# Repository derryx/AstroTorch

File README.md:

# Astro-Torch

## Bestellnummern von Reichelt

* ATTINY 24A-SSU ( +2.7 ... +5.5 V, SOIC-14)
* LED 5-8000 RT (Kingbright L-7113SRC-J4, 2.5V, 20mA)
* LED EL 5-14250KW (Everlight 334-15/T2C3-2TVC/EU, 3.6V, 20mA)
* MCP 1703T-3302E (MCP1703T-3302E/CB, Low-Power Regulator 3.3V, SOT-23A)
* IRLML 2502 (IRLML2502TRPBF, N-Ch-Mosfet logic-level, SOT-23)
* Rotary Encoder STEC12E08 (402097) + Knopf KNOPF 13-164E (861036)
* Gehäuse SP 6090 SW 

Für den LDO Regulator 2X 1 uF Ceramic KEM 0805 1U (C0805C105K4RACAUTO, 0805 Bauform)

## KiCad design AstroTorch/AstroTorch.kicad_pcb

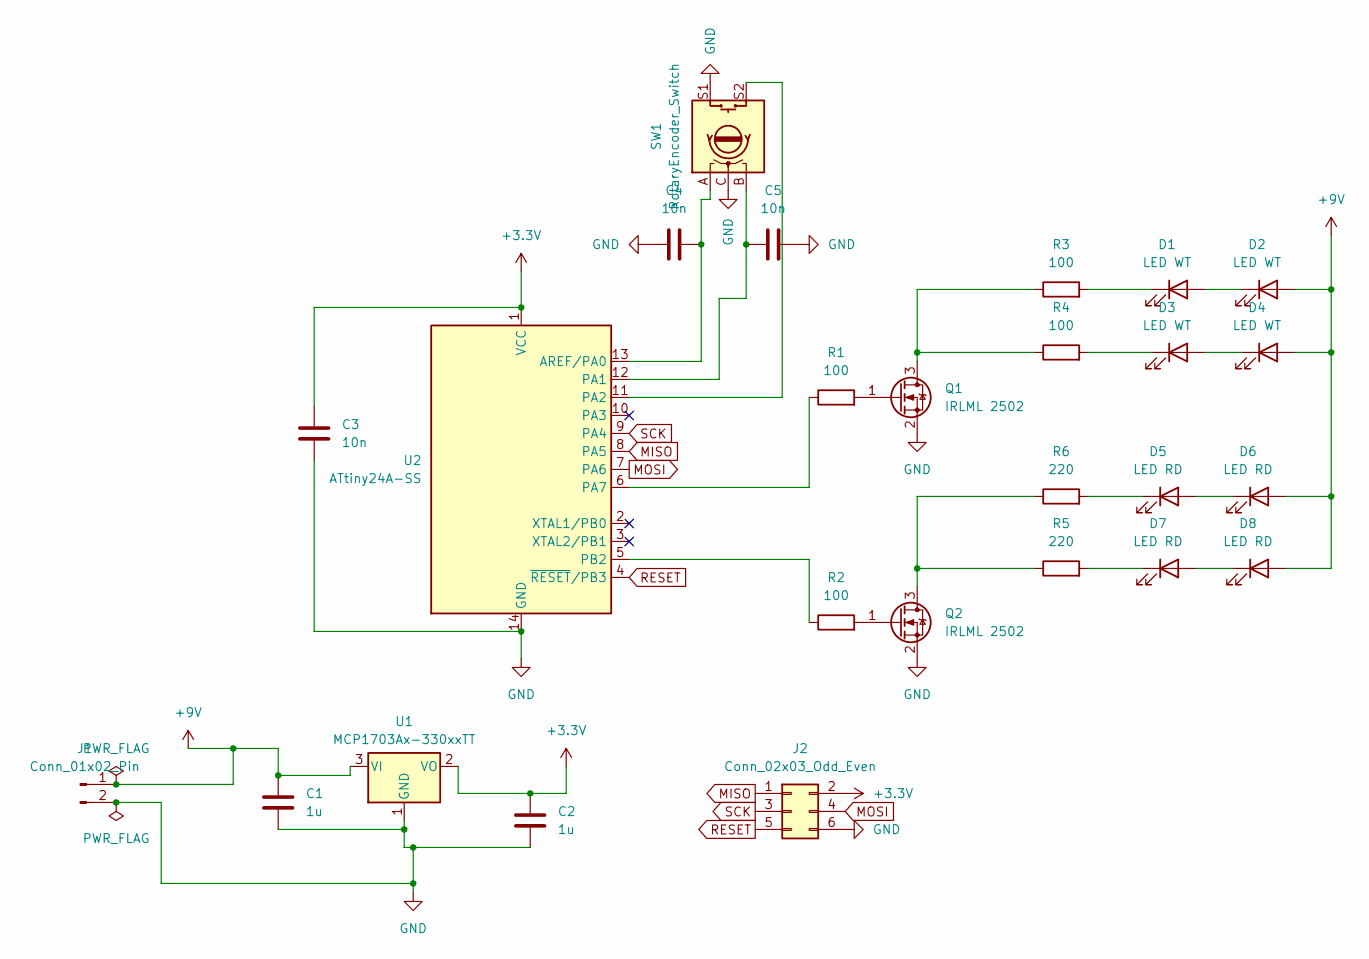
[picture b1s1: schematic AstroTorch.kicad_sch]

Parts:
C1, C2: 1u; C_0805_2012Metric
C3, C4, C5: 10n; C_0805_2012Metric
D1, D2, D3, D4: LED WT; LED_D5.0mm
D5, D6, D7, D8: LED RD; LED_D5.0mm
J1: Conn_01x02_Pin; PinHeader_1x02_P2.54mm_Vertical
J2: Conn_02x03_Odd_Even; PinHeader_2x03_P2.54mm_Vertical_SMD
Q1, Q2: IRLML 2502; SOT-23
R1, R2, R3, R4: 100; R_0805_2012Metric
R5, R6: 220; R_0805_2012Metric
SW1: RotaryEncoder_Switch; RotaryEncoder_Alps_EC11E-Switch_Vertical_H20mm
U1: MCP1703Ax-330xxTT; SOT-23
U2: ATtiny24A-SS; SOIC-14_3.9x8.7mm_P1.27mm

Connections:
+3.3V: C2.1, C3.1, J2.2, U1.2 (VO), U2.1 (VCC)
+9V: C1.1, D2.2 (A), D4.2 (A), D6.2 (A), D8.2 (A), J1.1, U1.3 (VI)
GND: C1.2, C2.2, C3.2, C4.1, C5.2, J1.2, J2.6, Q1.2 (S), Q2.2 (S), SW1.C, SW1.S1, U1.1 (GND), U2.14 (GND)
MISO: J2.1, U2.8 (PA5)
MOSI: J2.4, U2.7 (PA6)
unnamed: D1.2 (A), D2.1 (K)
unnamed: D1.1 (K), R3.2
unnamed: D3.2 (A), D4.1 (K)
unnamed: D3.1 (K), R4.2
unnamed: D5.2 (A), D6.1 (K)
unnamed: D5.1 (K), R6.2
unnamed: D7.2 (A), D8.1 (K)
unnamed: D7.1 (K), R5.2
unnamed: Q1.3 (D), R3.1, R4.1
unnamed: Q1.1 (G), R1.2
unnamed: Q2.3 (D), R5.1, R6.1
unnamed: Q2.1 (G), R2.2
unnamed: C4.2, SW1.A, U2.13 (AREF/PA0)
unnamed: C5.1, SW1.B, U2.12 (PA1)
unnamed: SW1.S2, U2.11 (PA2)
unnamed: R1.1, U2.6 (PA7)
unnamed: R2.1, U2.5 (PB2)
RESET: J2.5, U2.4 (~RESET/PB3)
SCK: J2.3, U2.9 (PA4)

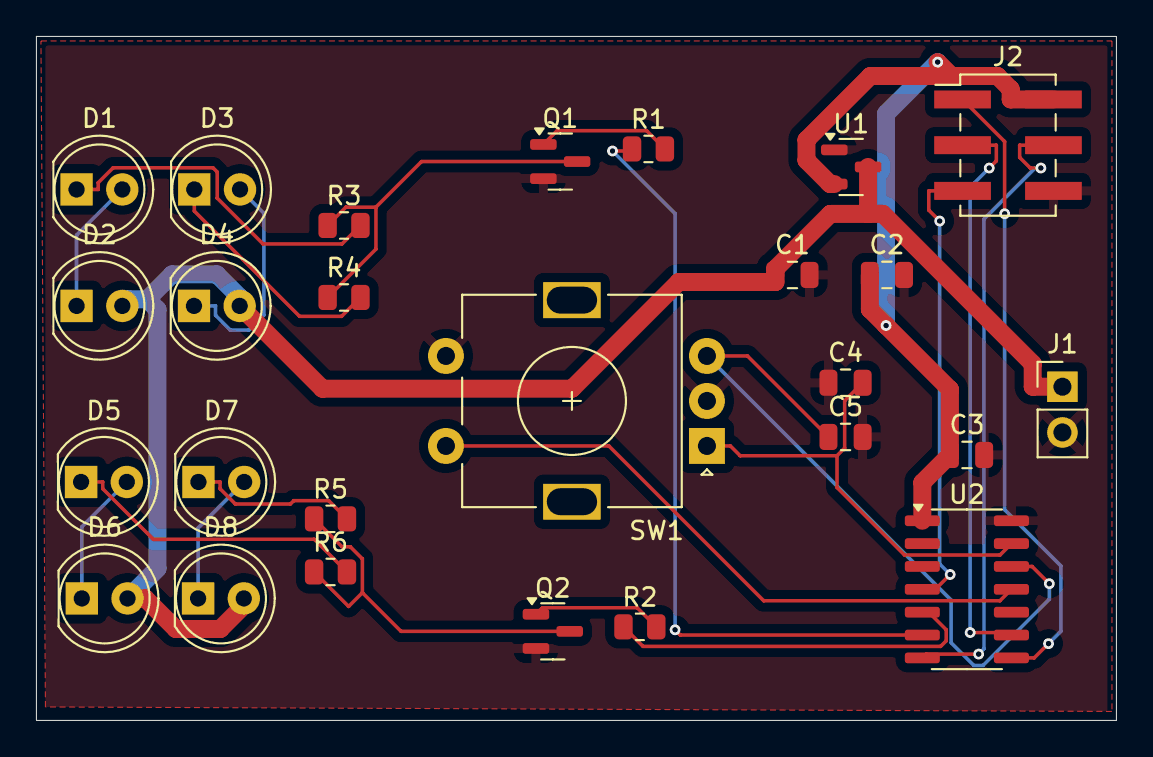
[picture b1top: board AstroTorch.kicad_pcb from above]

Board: 2 copper layers, 60.0 x 38.0 mm, 26 parts (0 on the bottom side), 24 nets.

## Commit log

2025-05-28 Add license
2025-05-28 First stuff
2025-05-28 Next version
2025-05-28 Added case
